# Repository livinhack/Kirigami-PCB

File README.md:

# Kirigami PCB Mod

This mod adds two PCBs ([Frame PCB](#frame-pcb), [Kirigami PCB](#kirigami-pcb)) and a cable ([Cable](#cable-and-chain)) to the V0.1/V0.2 that can aid in wire management and routing.

There are also optional things like a [Bed Fan](https://github.com/livinhack/Kirigami_PCB/tree/main/Optional/Bed_Fan) or a [Kirigami-Front](https://github.com/livinhack/Kirigami_PCB/tree/main/Optional/Front).

----

# Frame PCB
The frame PCB mounts on the side in the electronics bay of the printer and combines all cables into a single 10 pin Micro-Fit 3.0 connector. (With neopixel loop-through.)

## Frame PCB BOM
| Part                        | Quantity V1/V2 | Notes           | LCSC Part Number | Link                                                                                                               |
| --------------------------- |      :-:       | --------------- | ---------------- |------------------------------------------------------------------------------------------------------------------- |
| 10 Pin Socket (Right Angle) | 1              | MOLEX 430451000 | C122421          | [lcsc](https://www.lcsc.com/product-detail/Wire-To-Board-Wire-To-Wire-Connector_MOLEX-430451000_C122421.html)              |
| 2 pin JST XH                | 2              | 2.5mm pitch     | C158012          | [lcsc](https://lcsc.com/product-detail/Wire-To-Board-Wire-To-Wire-Connector_JST-Sales-America-B2B-XH-A-LF-SN_C158012.html) |
| 3 pin JST XH                | 2              | 2.5mm pitch     | C144394          | [lcsc](https://lcsc.com/product-detail/Wire-To-Board-Wire-To-Wire-Connector_JST-Sales-America-B3B-XH-A-LF-SN_C144394.html) |
| Screw Terminal              | 1              | 5.08mm pitch    |                  | [digikey](https://www.digikey.de/en/products/detail/metz-connect-usa-inc/31101102/7794830)                                    |
| Screw M3x8                  | 2              |                 |                  |                                                                                                                    |
| Nut M3                      | 2              |                 |                  |                                                                                                                    |
----

# Kirigami PCB

Mounted on the Kirigami bed mount, this breaks out the 10 pin harness into all needed connectors.

## Kirigami PCB BOM
| Part                        | Quantity V1 | Quantity V2 | Notes           | LCSC Part Number | Link                                                                                                               |
| --------------------------- |     :-:     |     :-:     | --------------- | ---------------- |------------------------------------------------------------------------------------------------------------------- |
| 10 Pin Socket (Right Angle) | 1           | 1           | MOLEX 430451000 | C122421          | [lcsc](https://www.lcsc.com/product-detail/Wire-To-Board-Wire-To-Wire-Connector_MOLEX-430451000_C122421.html)              |
| 2 pin JST XH                | 4           | 3           | B2B-XH          | C158012          | [lcsc](https://lcsc.com/product-detail/Wire-To-Board-Wire-To-Wire-Connector_JST-Sales-America-B2B-XH-A-LF-SN_C158012.html) |
| 4 pin JST XH                | 1           | 1           | B4B-XH          | C144395          | [lcsc](https://lcsc.com/product-detail/Wire-To-Board-Wire-To-Wire-Connector_JST-Sales-America-B4B-XH-A-LF-SN_C144395.html) |
| Screw Terminal              |             | 1           | 5.08mm pitch    |                  | [digikey](https://www.digikey.de/en/products/detail/metz-connect-usa-inc/31101102/7794830)                                    |
| Screw M3x6                  | 8           | 8           | *(Or M3x8)*     |                                                                                                                                       |
| Heat-Set Inserts            | 8           | 8           | Voron-spec      |                                                                                                                                       |

### Optional Parts
| Part                | Quantity | Notes                            | LCSC Part Number | Link                                                                                                                             |
| ------------------- |   :-:    | -------------------------------- | ---------------- |--------------------------------------------------------------------------------------------------------------------------------- |
| 0805 10uF Capacitor |  1       | Use if using BARE neopixel IC's. | C162422           | [lcsc](https://www.lcsc.com/product-detail/_Murata-Electronics-_C162422.html) |

## [Optional Bed Fan](https://github.com/livinhack/Kirigami_PCB/tree/main/Optional/Bed_Fan)

## [Optional Front](https://github.com/livinhack/Kirigami_PCB/tree/main/Optional/Front)

## [For the RGB lovers among us: Kirigami U.F.O.](https://github.com/livinhack/Kirigami_U.F.O)

### If you have a Neopixel in your Kirigami front, please note the following:

---

# Cable and chain

The Cable is a dual ended 10P (2x5) microfit cable. The connectors are wired 1:5, 6:10 so pin 1 connects to pin 5, pin 2 connects to pin 4 and so forth for all 10 pins.

*Only 2 of the 10 wires are shown for clarity. Connect each number to its opposite. (in it's row!)*

Symbolic representation of the connection:

## Cable BOM
| Part           | Quantity | Notes                                          | LCSC Part Number | Link                                                                                             |
| -------------- |    :-:   | ---------------------------------------------- | ---------------- |------------------------------------------------------------------------------------------------- |
| 10 Pin Plug    | 2        | Molex 430251400                                | C259745          | [lcsc](https://www.lcsc.com/product-detail/Rectangular-Connectors-Housings_MOLEX-430251000_C259745.html) |
| Microfit Crimp | 20       | Molex 430300001                                | C259786          | [lcsc](https://lcsc.com/product-detail/Line-Pressing-Terminals_MOLEX-430300001_C259786.html)             |
| Wire           | 10       | Smallest required AWG per respective function. |                  | PTFE/Silicone/Hefulon for motion rated                                                           |
### Note: Don't use 20 AWG wire on all ten!(!!!) It works, but it's a s**t job... Ask me how I know...

### Note: You don't need the chain-end spacer if your chain is "V0.1-spec"!
| Part  | Part Number  | Link                                                                                |
| ------| ------------ |------------------------------------------------------------------------------------ |
| Chain | E04.07.015.0 | [igus](https://www.igus.eu/iPro/iPro_01_0009_0001_GBen.htm?ArtNr=E04.07.015.0&c=DE&l=en)    |
|       |              | [lecktor](https://lecktor.com/en/v0-cables-connectors/716-igus-v02-chain-e04070150-00716.html) |

-----

# Change Log #

## V2+:
 - Link to U.F.O. variant

## V2:
 - Moved Screw Terminal postition on Frame PCB and rearranged positons of the connectors + changing heater to Screw Terminal on the Kirigami PCB

## V1:
 - Initial Idea

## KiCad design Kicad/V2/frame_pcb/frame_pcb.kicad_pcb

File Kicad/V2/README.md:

| PCB                                                    | SCH                                                    |
| ------------------------------------------------------ |------------------------------------------------------- |
|   |   |
|  |  |

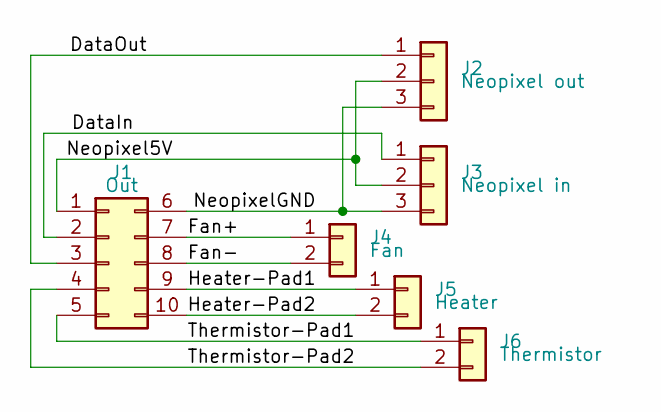
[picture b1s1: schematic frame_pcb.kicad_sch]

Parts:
J1: Out; Molex_Micro-Fit_3.0_43045-1000_2x05_P3.00mm_Horizontal
J2: Neopixel out; JST_XH_B3B-XH-A_1x03_P2.50mm_Vertical
J3: Neopixel in; JST_XH_B3B-XH-A_1x03_P2.50mm_Vertical
J4: Fan; JST_XH_B2B-XH-A_1x02_P2.50mm_Vertical
J5: Heater; METZ CONNECT USA Inc. - TERM BLK 2P SIDE ENT 5.08MM PCB
J6: Thermistor; JST_XH_B2B-XH-A_1x02_P2.50mm_Vertical

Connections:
/DataIn: J1.2, J3.1
/DataOut: J1.3, J2.1
/Fan+: J1.7, J4.1
/Fan-: J1.8, J4.2
/Heater-Pad1: J1.9, J5.1
/Heater-Pad2: J1.10, J5.2
/Neopixel5V: J1.1, J2.2, J3.2
/NeopixelGND: J1.6, J2.3, J3.3
/Thermistor-Pad1: J1.5, J6.1
/Thermistor-Pad2: J1.4, J6.2

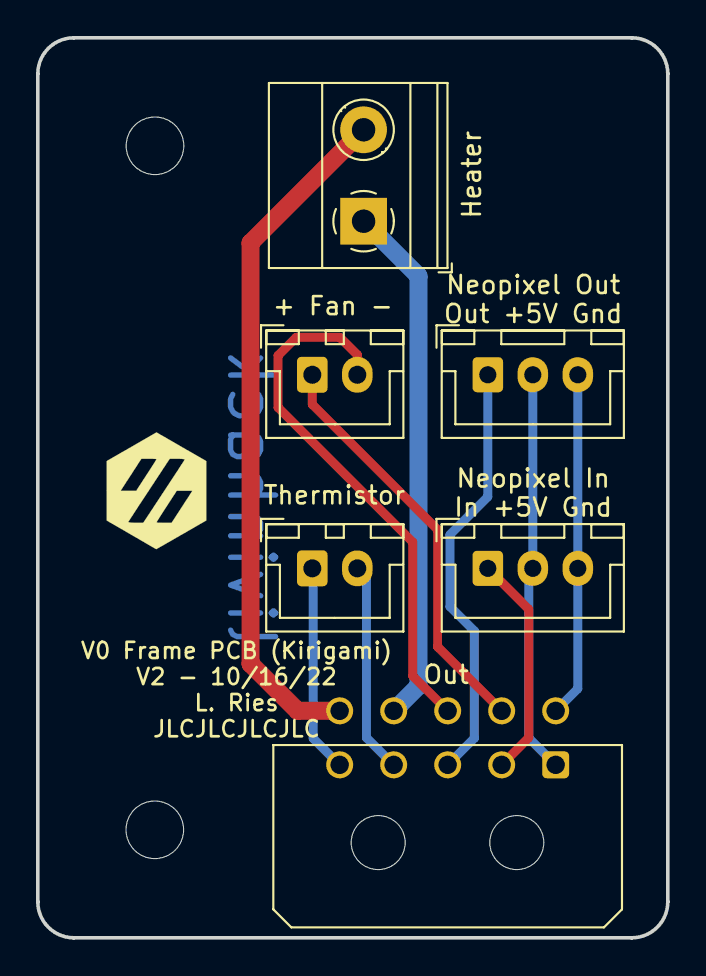
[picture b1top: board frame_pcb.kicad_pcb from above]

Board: 2 copper layers, 35.0 x 50.0 mm, 8 parts (0 on the bottom side), 10 nets.

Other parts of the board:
H1, H2: MountingHole_3.2mm_M3

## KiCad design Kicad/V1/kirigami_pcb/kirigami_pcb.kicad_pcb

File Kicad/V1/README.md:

| PCB                                                    | SCH                                                    |
| ------------------------------------------------------ |------------------------------------------------------- |
|   |   |
|  |  |

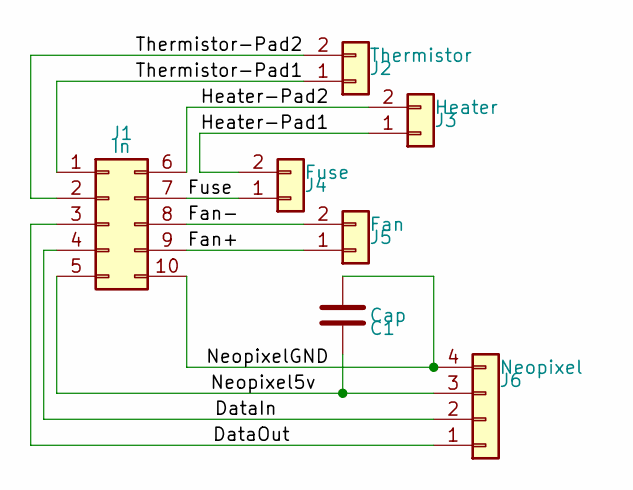
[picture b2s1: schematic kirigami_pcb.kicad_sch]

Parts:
C1: Cap; C_0805_2012Metric_Pad1.18x1.45mm_HandSolder
J1: In; Molex_Micro-Fit_3.0_43045-1000_2x05_P3.00mm_Horizontal
J2: Thermistor; JST_XH_B2B-XH-A_1x02_P2.50mm_Vertical
J3: Heater; JST_XH_B2B-XH-A_1x02_P2.50mm_Vertical
J4: Fuse; JST_XH_B2B-XH-A_1x02_P2.50mm_Vertical
J5: Fan; JST_XH_B2B-XH-A_1x02_P2.50mm_Vertical
J6: Neopixel; JST_XH_B4B-XH-A_1x04_P2.50mm_Vertical

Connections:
/DataIn: J1.4, J6.2
/DataOut: J1.3, J6.1
/Fan+: J1.9, J5.1
/Fan-: J1.8, J5.2
/Fuse: J1.7, J4.1
/Heater-Pad1: J3.1, J4.2
/Heater-Pad2: J1.6, J3.2
/Neopixel5v: C1.1, J1.5, J6.3
/NeopixelGND: C1.2, J1.10, J6.4
/Thermistor-Pad1: J1.1, J2.1
/Thermistor-Pad2: J1.2, J2.2

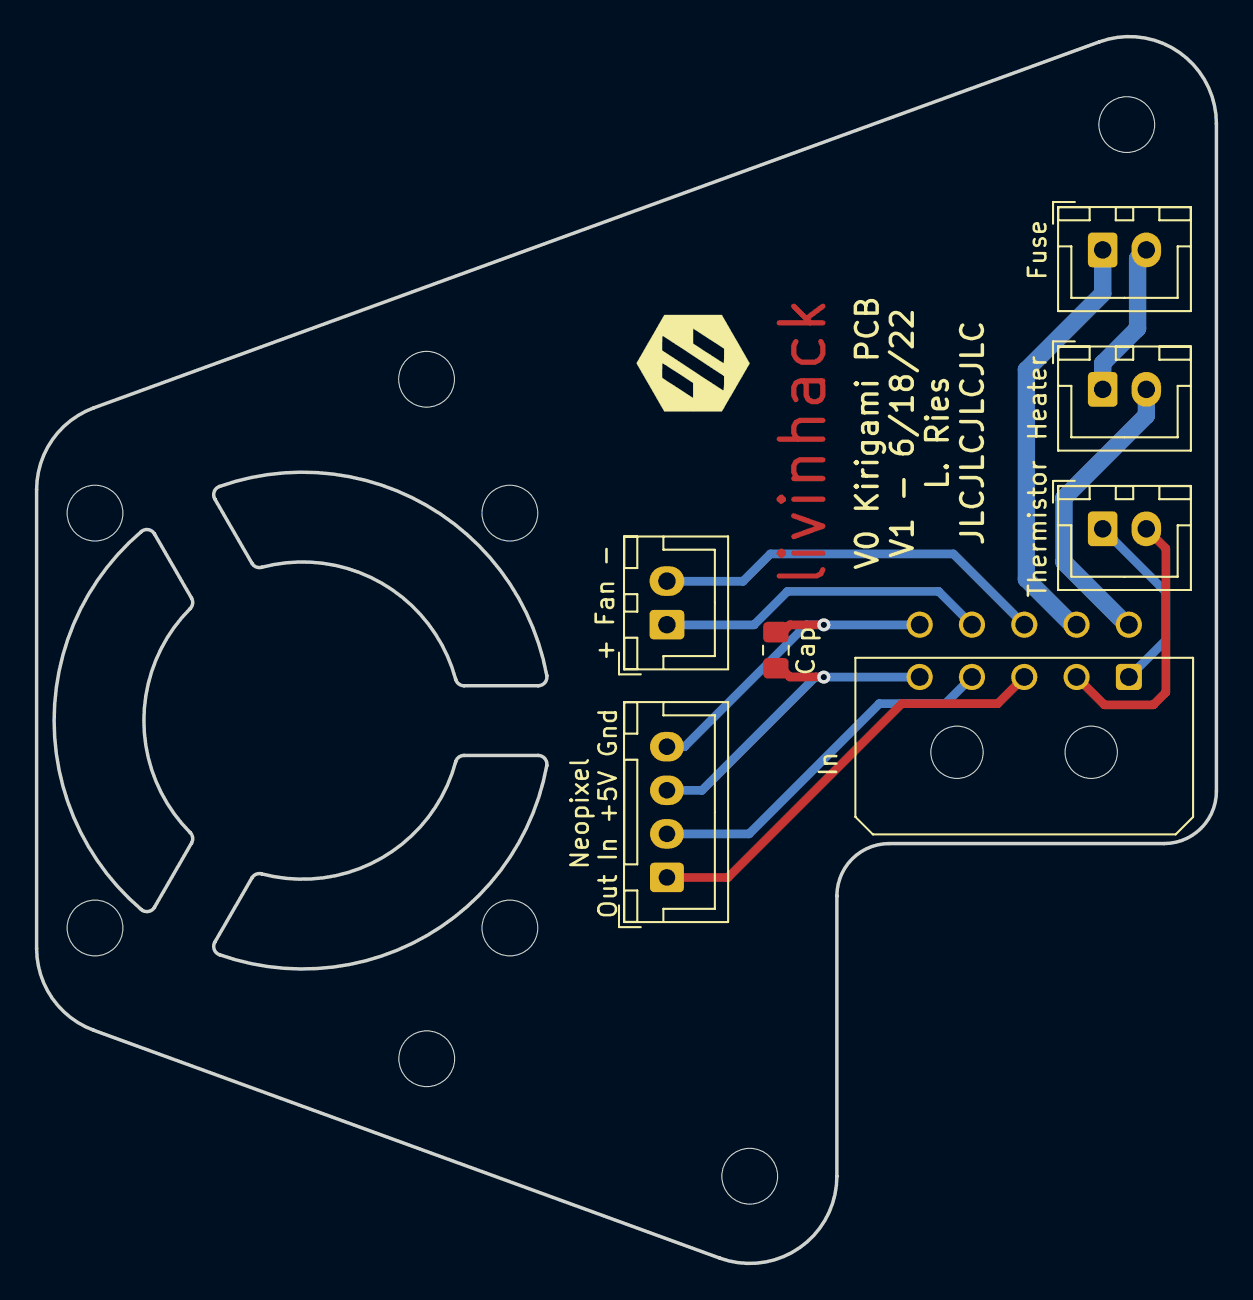
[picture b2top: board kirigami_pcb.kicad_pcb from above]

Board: 2 copper layers, 67.7 x 70.4 mm, 15 parts (0 on the bottom side), 11 nets.

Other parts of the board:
H1, H2, H3, H4, H5, H6, H7, H8: MountingHole_3.2mm_M3

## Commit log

2024-04-08 Update README.md
    Clarify UFO case
2024-04-08 Update README.md
    V > Option
2024-04-08 rename
